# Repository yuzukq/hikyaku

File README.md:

# hikyaku（飛脚）

手持ちの USB キーボードの入力を受け取り、Bluetooth (BLE) で Mac に届ける無線中継器。
トラックパッドも内蔵し、分割キーボードの真ん中に置いて使うことを想定している。

```
[USB キーボード] --USB--> [hikyaku: ESP32-S3 + TM035035] --BLE HID--> [Mac]
                                   ↑
                             トラックパッド
```

## 構成

| 役割 | 部品 | メモ |
|---|---|---|
| マイコン | ESP32-S3 SuperMini（USB-C 1 ポート。ESP32-S3FH4R2 搭載。GPIO48 に RGB LED。AliExpress 品） | USB OTG でホストになれる + BLE。1チップで完結 |
| トラックパッド | Cirque Pinnacle TM035035（SPI 版） | 35mm 円形。J1 は 12 ピン 0.5mm FFC |
| USB 接続 | USB-C ⇔ USB-C ケーブル | ESP32-S3 ボードの USB-C をホストポートとして使う |
| 電源・ログ | 秋月 AE-CH9102F-TYPEC-BO（USB-シリアル変換） | USB-C にモバイルバッテリー（または PC）をつなぎ、+5V を S3 の 5V ピンへ（キーボードにも届く）。ログの取り出し口も兼ねる |

部品の詳細と手持ちの状況は [docs/hardware/parts.md](docs/hardware/parts.md)。

## 設計上の決定

- **マイコンは ESP32-S3**：nRF52840 は USB ホスト非対応のため不採用。ESP32-C3 も USB ホスト不可（Serial/JTAG のデバイス側のみ）で不採用。BLE 検証には使った
- **言語は Rust**（esp-hal + embassy + trouble）。USB ホストは esp-hal の OTG ホストドライバ + `embassy-usb-host`
- **一次電池は使わない**：USB キーボードへの 5V 給電を含めると全体で約 100mA 前後になり、コイン電池では動かず、乾電池では交換頻度が高い
- **ESP32-S3 の BLE は macOS で安定して動作した**（ボンディング保存・再起動後の自動再接続も確認済み）。nRF52840 は不要
- **HID レポートは詰め替える**：受け取ったキーボードのレポート記述子をそのまま流さず、固定の記述子（キーボード + コンシューマ + マウス）に変換する。キーボードごとに記述子が変わると macOS のペアリングキャッシュで不具合が出るため

## 既知の制約

- ボードの 5V ピンから外部給電すると、USB-C のポート経由でキーボードにも 5V が届く（動作確認済み）。ホスト動作中はここに外部から 5V を入れる
- 電池駆動ではボード単体では VBUS に 5V は出ない。モバイルバッテリー（5V）か昇圧モジュールが必要
- USB-C をホストに使うと USB CDC のシリアルログが使えない。デバッグは UART（USB-シリアル変換）で行う。キーボードを使わない間は、`usb-log` の版で S3 の USB-C から直接ログを読める（[docs/firmware.md](docs/firmware.md)）

## 現状

**v1 完成（2026-10-15）。** ユニバーサル基板に組んだ状態で、7skb（USB）→ S3（USB ホスト）→ BLE → Mac のパススルー（通常キー・メディアキー・マウス系、ボンディング保存つき）と、トラックパッド（相対モード、感度 2X、タップ = クリック）が同時に動作する。起動時は LED が赤（触らない）→ 緑（準備完了）。

モバイルバッテリーでの動作も確認済み。

その後、F24 / 本体のボタン（GPIO6 の MX スイッチ）によるスクロール、Mac アプリのショートカットリング、本体の向きの設定、TOFU60 への対応が加わった。

残り: PCB 化（回路図まで。[docs/hardware/pcb.md](docs/hardware/pcb.md)）、ケース、電力まわりの最適化、長時間の自動オフの確認、2 台切り替え（構想）。

- 進捗と今後の計画: [ROADMAP.md](ROADMAP.md)
- 資料（配線・電源・仕様メモ・ビルド/書き込み手順・落とし穴）: [docs/](docs/README.md)

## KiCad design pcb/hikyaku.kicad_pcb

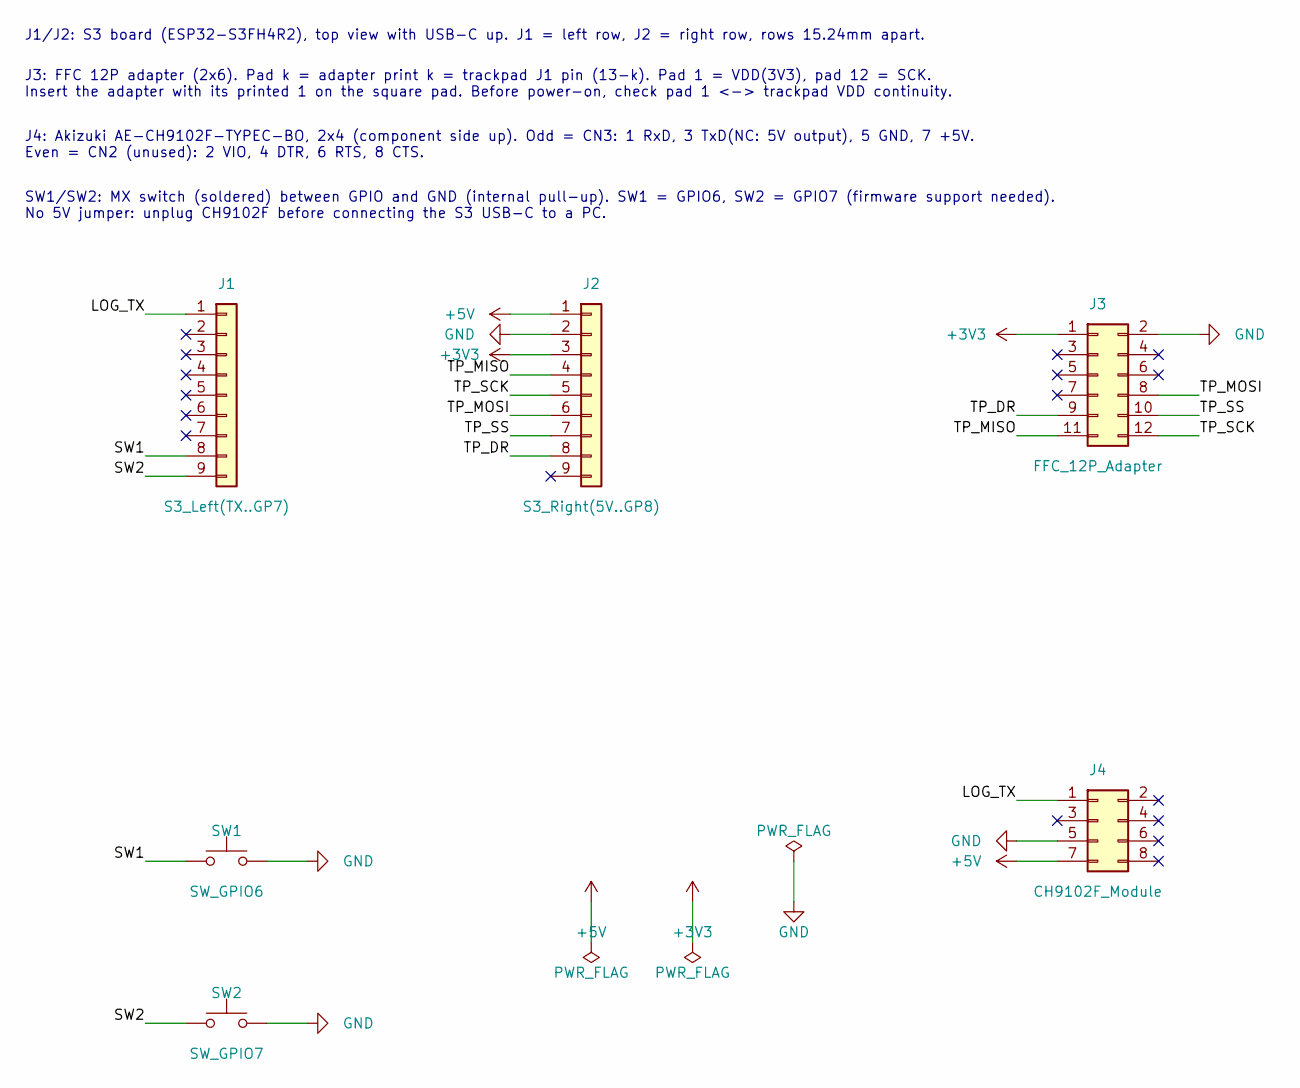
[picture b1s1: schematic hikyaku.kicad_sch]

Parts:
J1: S3_Left(TX..GP7); PinSocket_1x09_P2.54mm_Vertical
J2: S3_Right(5V..GP8); PinSocket_1x09_P2.54mm_Vertical
J3: FFC_12P_Adapter; PinSocket_2x06_P2.54mm_Vertical
J4: CH9102F_Module; PinSocket_2x04_P2.54mm_Vertical
SW1: SW_GPIO6; CherryMX_Solder_1u
SW2: SW_GPIO7; CherryMX_Solder_1u

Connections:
+3V3: J2.3, J3.1
+5V: J2.1, J4.7
/LOG_TX: J1.1, J4.1
/SW1: J1.8, SW1.1
/SW2: J1.9, SW2.1
/TP_DR: J2.8, J3.9
/TP_MISO: J2.4, J3.11
/TP_MOSI: J2.6, J3.8
/TP_SCK: J2.5, J3.12
/TP_SS: J2.7, J3.10
GND: J2.2, J3.2, J4.5, SW1.2, SW2.2

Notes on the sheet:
J4: Akizuki AE-CH9102F-TYPEC-BO, 2x4 (component side up). Odd = CN3: 1 RxD, 3 TxD(NC: 5V output), 5 GND, 7 +5V. Even = CN2 (unused): 2 VIO, 4 DTR, 6 RTS, 8 CTS.
J1/J2: S3 board (ESP32-S3FH4R2), top view with USB-C up. J1 = left row, J2 = right row, rows 15.24mm apart.
SW1/SW2: MX switch (soldered) between GPIO and GND (internal pull-up). SW1 = GPIO6, SW2 = GPIO7 (firmware support needed). No 5V jumper: unplug CH9102F before connecting the S3 USB-C to a PC.
J3: FFC 12P adapter (2x6). Pad k = adapter print k = trackpad J1 pin (13-k). Pad 1 = VDD(3V3), pad 12 = SCK. Insert the adapter with its printed 1 on the square pad. Before power-on, check pad 1 <-> trackpad VDD continuity.

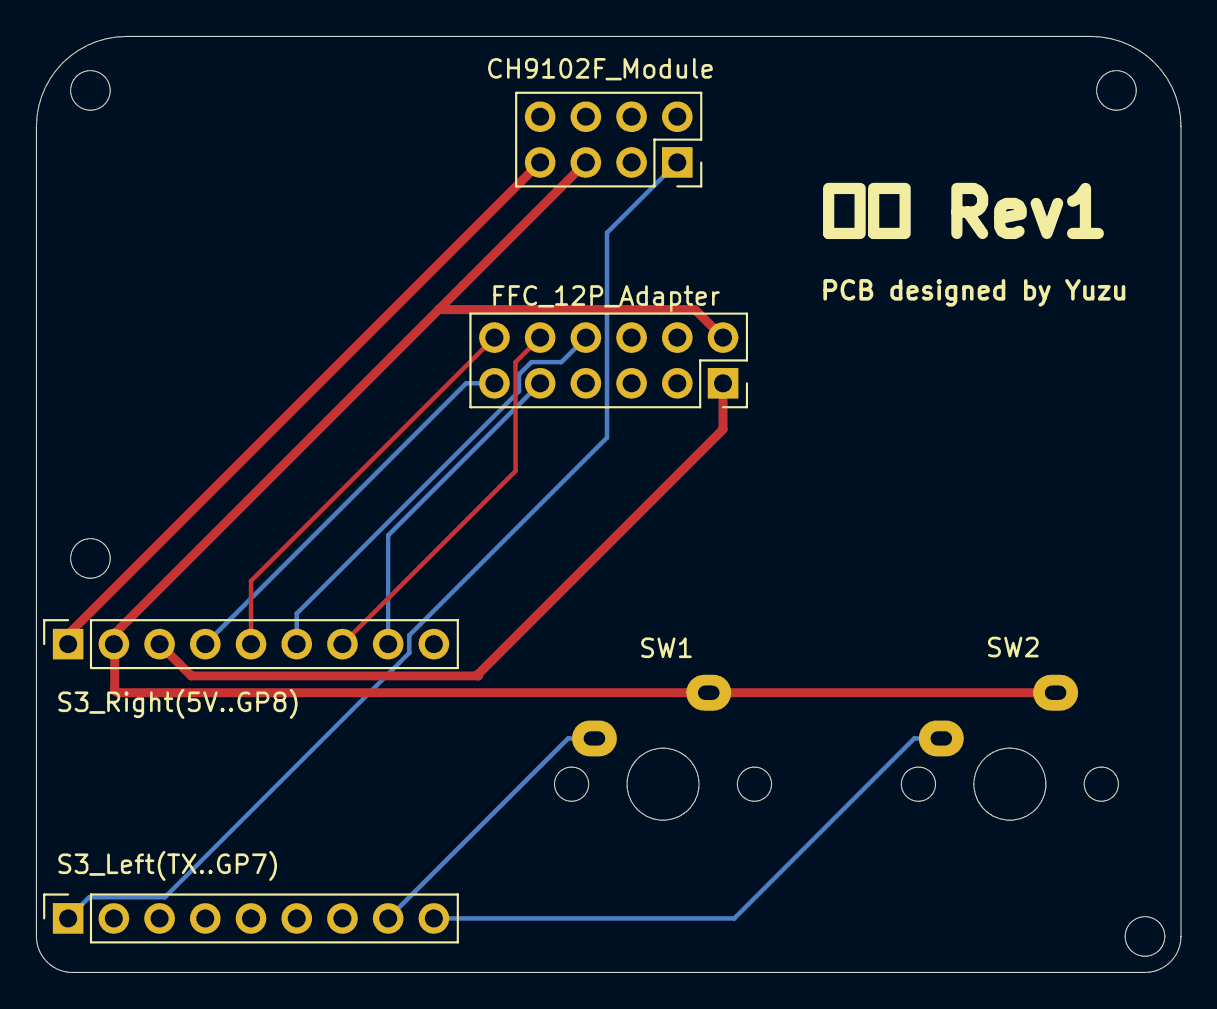
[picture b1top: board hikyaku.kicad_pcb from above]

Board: 2 copper layers, 63.6 x 52.0 mm, 6 parts (0 on the bottom side), 11 nets.
